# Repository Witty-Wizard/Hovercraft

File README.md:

<p align="center">

</p>

# Hovercraft
Welcome to our project repository! Here you'll find all the resources, documentation, and source code related to our project.

## About Hovercraft

This hovercraft was designed using 2 2400 emax 2207 motors , xylo 40A ESC and ESP32.

The Esp32 is responsible for decoding the sbus signal from the reciever and then produce the output signals for motor. The main reason of using ESP32 was so that we could reverse the direction of motor using 3d mode which is run over the dshot protocol. This nabled the hovercraft to go in the reverse direction if required even if that was with very less efficiency.

## Features
- Multiple rc protocol support including crsf and sbus.
- supports dshot output and motor reversibility .

with many more features on the way!

## Getting Started

### Setting up Development Enviorment
To set up your development environment, follow these steps:

1. Install Visual Studio Code (VS Code):
- Download and install VS Code from the [official website](https://code.visualstudio.com/).

2. Install PlatformIO Extension:
- Open VS Code.
- Go to the Extensions view by clicking on the square icon in the sidebar or pressing Ctrl+Shift+X.
- Search for "PlatformIO" in the Extensions Marketplace.
- Click on "Install" to install the PlatformIO extension.
- Restart VS Code after installation is complete.

### Cloning the Repository
To get started with the project, follow these steps:

1. Clone the repository to your local machine:

    ```bash
    git clone https://github.com/Robotics-Society-PEC/Hovercraft.git
    ```
2. Open the project in Visual Studio Code (VS Code):

- Launch VS Code.
- Click on "File" > "Open Folder...".
- Navigate to the directory where you cloned the repository (Hovercraft) and select it.
- The project will open in VS Code, and you can start working on it.

## Contributing

We welcome contributions from the community! If you'd like to contribute, please follow these guidelines:

1. Fork the repository
2. Create your feature branch: 
    ```bash
    git checkout -b feature-name
    ```
3. Commit your changes:
    ```bash
    git commit -am 'Add some feature'
    ```

4. Push to the branch: 
    ``` bash
    git push origin feature-name
    ```
5. Submit a pull request

For major changes, please open an issue first to discuss what you would like to change.

## License
See the [LICENSE](LICENSE) file for details.

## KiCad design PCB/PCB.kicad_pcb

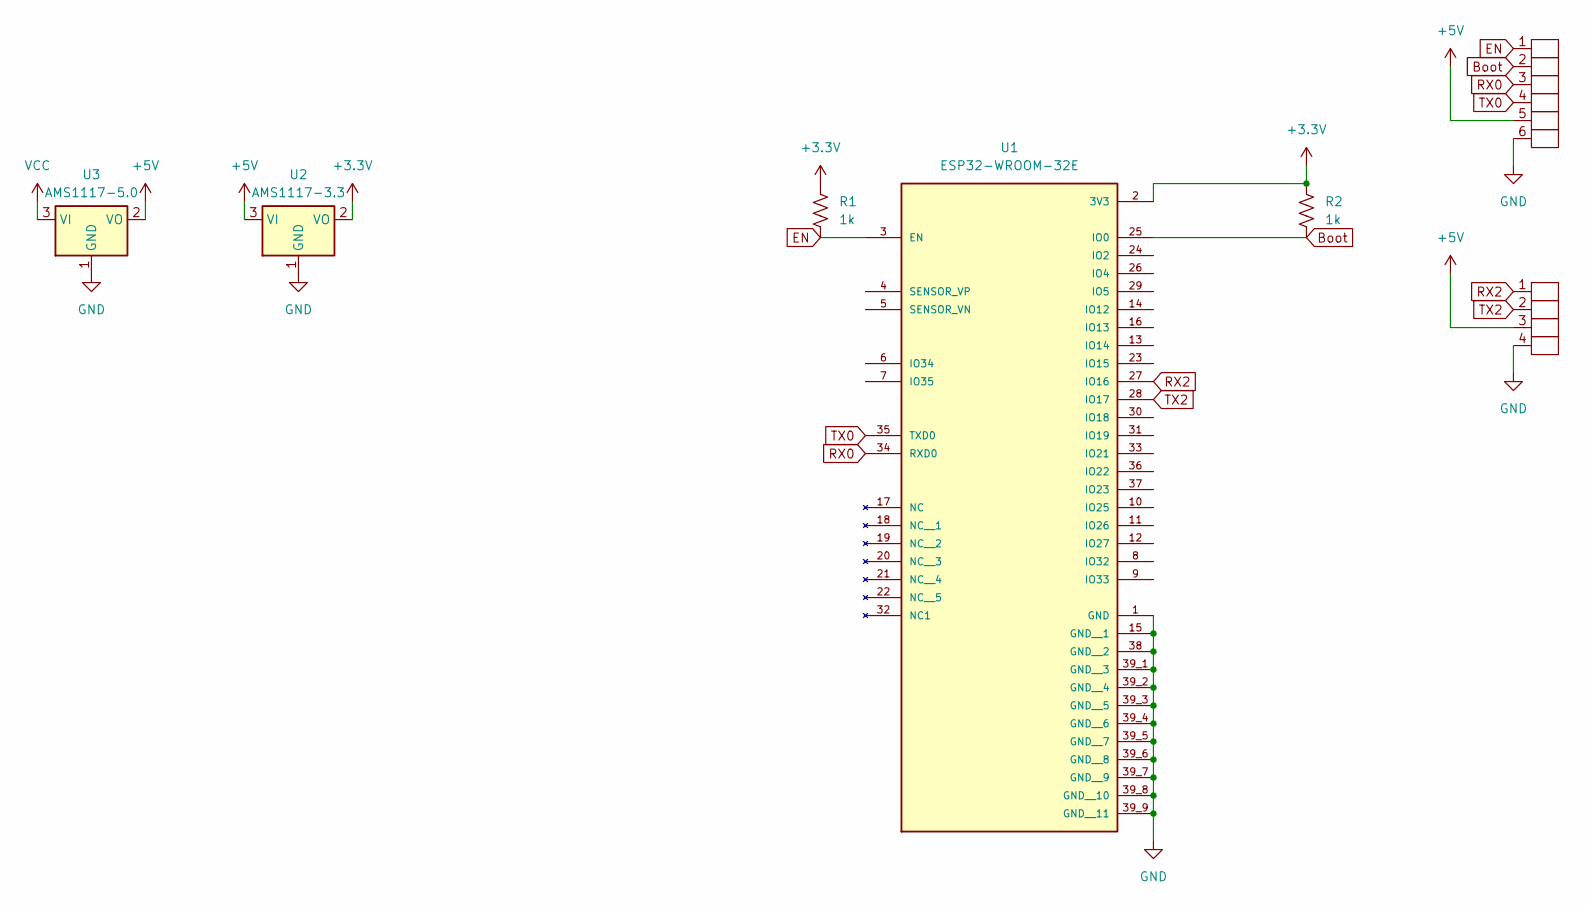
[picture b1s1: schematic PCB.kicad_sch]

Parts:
R1, R2: 1k; R_0805_2012Metric
U1: ESP32-WROOM-32E; PARTREV 1.4
U2: AMS1117-3.3; SOT-223-3_TabPin2
U3: AMS1117-5.0; SOT-223-3_TabPin2
s1: Serial_Device
s2: Programming_Pads; Programming pads

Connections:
+3.3V: R1.1, R2.1, U1.2 (3V3), U2.2 (VO)
+5V: U2.3 (VI), U3.2 (VO), s1.3, s2.5
Boot: R2.2, U1.25 (IO0), s2.2
EN: R1.2, U1.3 (EN), s2.1
GND: U1.1 (GND), U1.15 (GND__1), U1.38 (GND__2), U1.39_1 (GND__3), U1.39_2 (GND__4), U1.39_3 (GND__5), U1.39_4 (GND__6), U1.39_5 (GND__7), U1.39_6 (GND__8), U1.39_7 (GND__9), U1.39_8 (GND__10), U1.39_9 (GND__11), U2.1 (GND), U3.1 (GND), s1.4, s2.6
RX0: U1.34 (RXD0), s2.3
RX2: U1.27 (IO16), s1.1
TX0: U1.35 (TXD0), s2.4
TX2: U1.28 (IO17), s1.2
VCC: U3.3 (VI)

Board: 2 copper layers, 7 parts (2 on the bottom side), 9 nets, no tracks yet.

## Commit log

2023-03-15 Added Sbus decoding
2023-03-17 updated main code
2023-03-17 fixed code
2023-03-17 added calibration code
2023-03-17 calibration code complete
2023-03-18 added code for motors
    - added code for thruster motor
    - added code for rudder servo
    - added failsafe and frame lost protection
2023-03-18 some visual changes
2023-03-19 added DShot test code
2023-03-20 final code using pwm
2023-03-20 Final Code
2023-03-21 implmented running average bt without time cosnideration
2023-03-21 implmented failsafe
2023-04-03 added readme file
2023-04-03 Hovercraft 3d design files
2023-06-14 Shifted from arduino ide to platform io
2023-06-14 shifted to platform io
2023-06-14 fixed
2023-06-14 submodule
2023-06-14 updated .gitignore
2023-06-15 added code for dhsot
2023-09-14 made a library for esc protocols
2023-09-14 updated submodule
2023-09-14 removed dshot and sbus submodule
2023-09-14 removed submodule
2023-09-15 used esc headerfile
2023-09-16 added reverse functionality in code
2023-10-10 Changed Readme
2023-11-26 added pcb files and motor mount 3d files
2023-11-26 housekeeping changes
2024-02-21 added git workflow
2024-02-21 test
2024-02-22 trying to remove submodule
2024-02-22 changed build file
2024-02-22 changes build.yml
2024-02-22 fixed error
2024-02-22 fixed the error i thought i fixed
2024-02-26 restructuring pcb file
2024-03-05 added dshot library template
2024-03-06 made new library for serial and dshot
2024-03-06 finish esc.h first then fix serial_rx
2024-03-07 made some changes(still not complete)
2024-03-08 added read.md
2024-03-09 now git action uploads artifacts
2024-03-11 created a library called serialIO
2024-03-11 fixed compilation error
2024-03-11 added library.json
2024-03-11 added read me file
2024-03-12 made the library decode sbus and crsf
2024-03-13 added doxygen to serialio
2024-03-16 final changes in library
2024-03-16 published the library
2024-03-23 added DriveMaster
2024-03-23 dShot testing pending
2024-04-10 fixed readme
2024-05-21 Added gitpod
2024-06-16 [FIXED]:Compilation error
2024-06-16 [Added]:Pico target
